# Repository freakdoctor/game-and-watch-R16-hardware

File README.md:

# game-and-watch-hardware

Basé sur le superbe travail d'Upcicle-Electronics pour les contours du PCB et le placement de certains composants.

Tentative de faire rentrer le hardware d'une SNES Mini dans une Game & Watch dans l'espoir d'y faire tourner le remaster Super Nes des premiers Marios inclus dans Super Mario All Stars.

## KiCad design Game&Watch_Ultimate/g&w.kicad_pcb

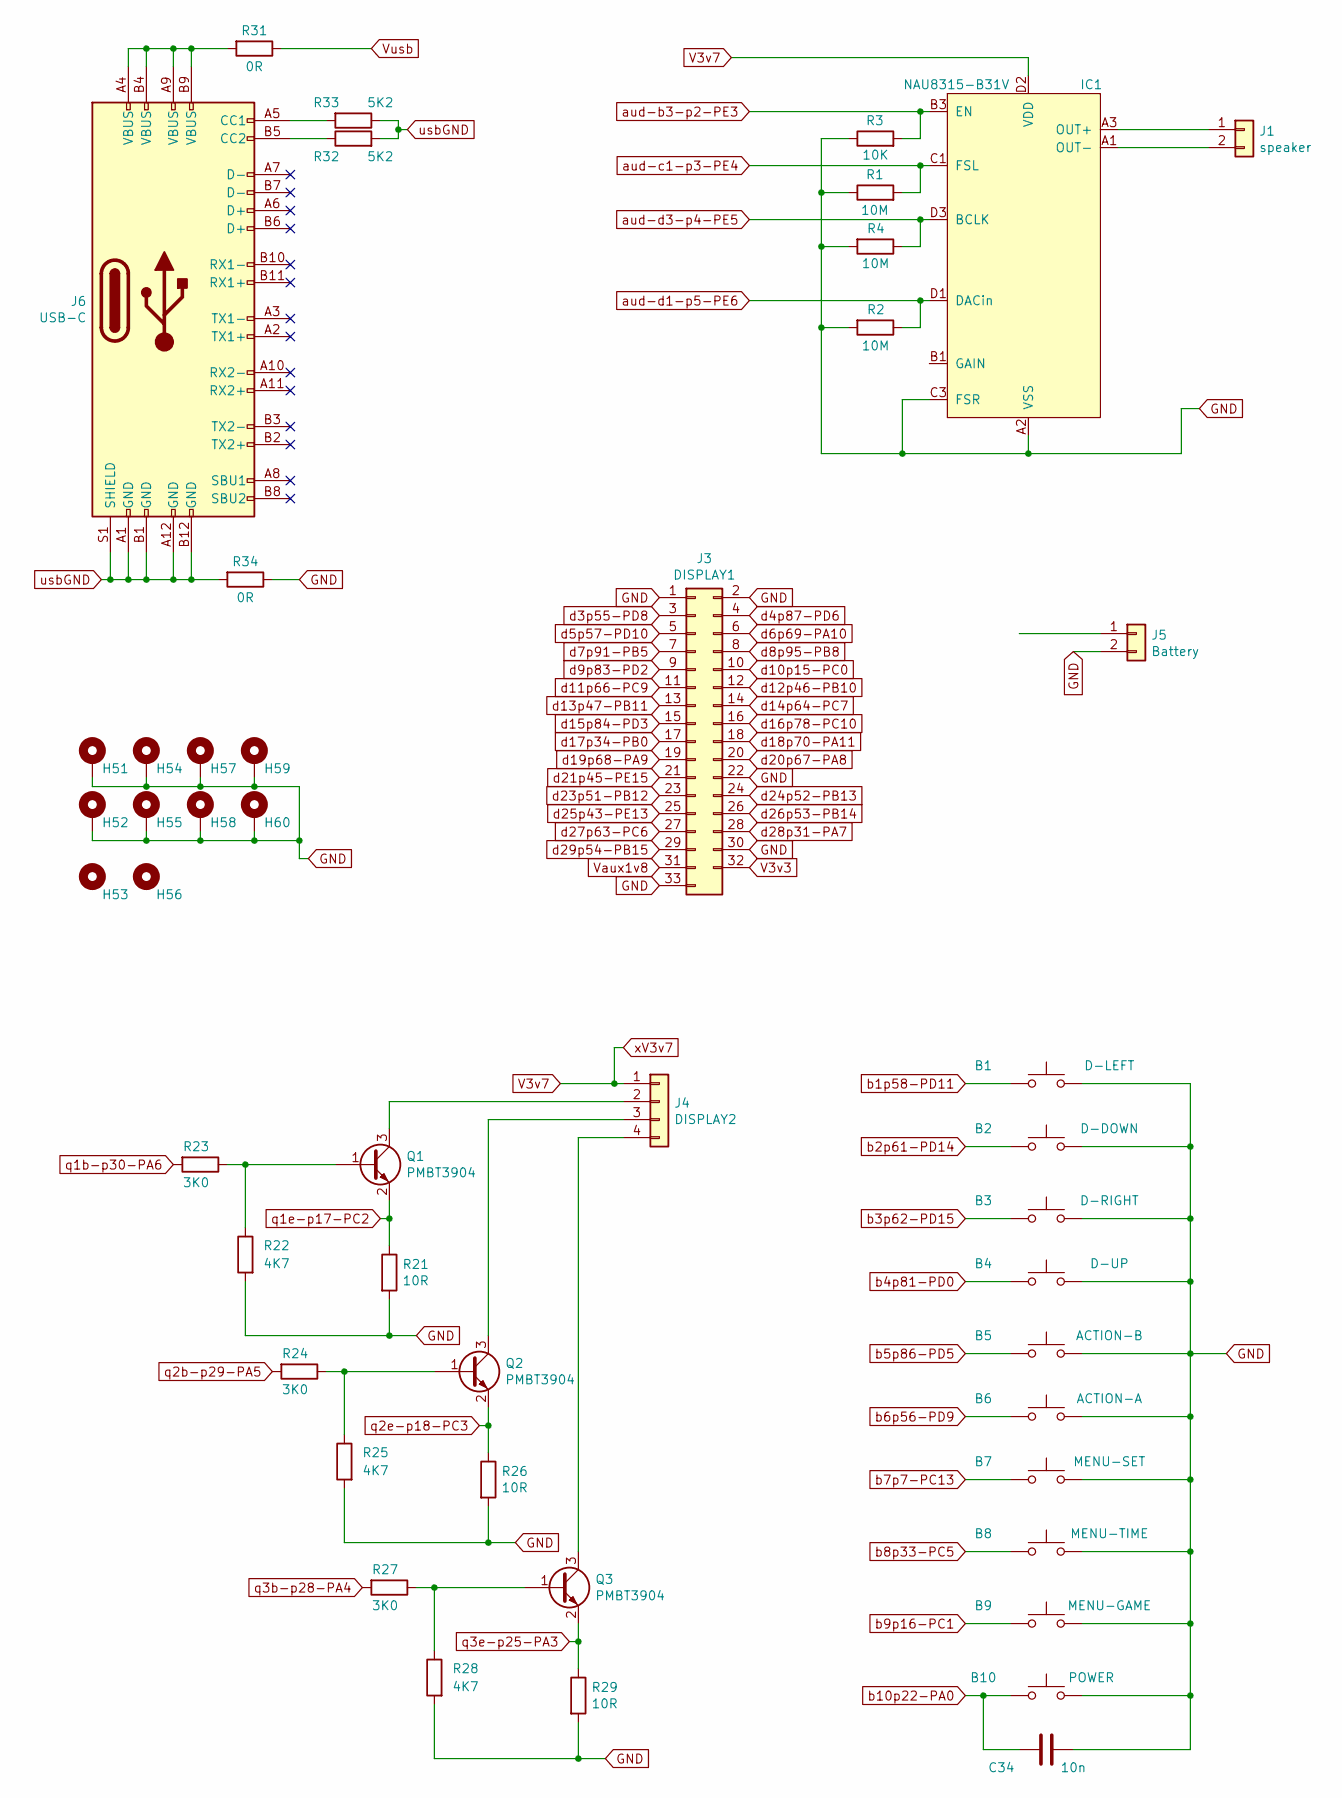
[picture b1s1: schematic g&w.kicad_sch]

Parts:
B1: D-LEFT; Button_Carbon-Contact_Round_5.00mm
B2: D-DOWN; Button_Carbon-Contact_Round_5.00mm
B3: D-RIGHT; Button_Carbon-Contact_Round_5.00mm
B4: D-UP; Button_Carbon-Contact_Round_5.00mm
B5: ACTION-B; Button_Carbon-Contact_Round_6.5mm
B6: ACTION-A; Button_Carbon-Contact_Round_6.5mm
B7: MENU-SET; Button_Carbon-Contact_Round_5.00mm
B8: MENU-TIME; Button_Carbon-Contact_Round_5.00mm
B9: MENU-GAME; Button_Carbon-Contact_Round_5.00mm
B10: POWER; SW_PUSH_1P1T_Horizontal_Nintendo_GnW
C34: 10n; C_0201_0603Metric
H51, H52, H54, H55, H57, H58, H59, H60: MountingHole_Pad; MountingHole_2.0mm
H53: MountingHole; MountingSlot_NC_1.3x2.2mm
H56: MountingHole; MountingHole_NC_1.5mm
IC1: NAU8315-B31V; WLCSP-12_1.18x1.95_Layout3x4_P0.4mm
J1: speaker; Speaker
J3: DISPLAY1; Molex_502078-3310_2Rows-33Pins-1MP_P0.5mm-int0.25mm_Horizon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
J4: DISPLAY2; Molex_Easy-On_503480-0400_1x04-1MP_P1.00mm_Horizontal
J5: Battery; Molex_Pico-EZmate_78171-0002_1x02-1MP_P1.20mm_Vertical
J6: USB-C; USB_C_Receptacle_JAE_DX07BN24JA2
Q1, Q2, Q3: PMBT3904; SOT-23
R1, R2, R4: 10M; R_0201_0603Metric
R3: 10K; R_0201_0603Metric
R21, R26, R29: 10R; R_0201_0603Metric
R22, R25, R28: 4K7; R_0201_0603Metric
R23, R24, R27: 3K0; R_0201_0603Metric
R31: 0R; R_0402_1005Metric
R32, R33: 5K2; R_0201_0603Metric
R34: 0R; R_0603_1608Metric

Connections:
GND: B1.2, B2.2, B3.2, B4.2, B5.2, B6.2, B7.2, B8.2, B9.2, B10.1, C34.2, H51.1, H52.1, H54.1, H55.1, H57.1, H58.1, H59.1, H60.1, IC1.A2 (VSS), IC1.C3 (FSR), J3.1, J3.2, J3.22, J3.30, J3.33, J5.2, R1.1, R2.2, R3.1, R4.2, R21.2, R22.2, R25.2, R26.2, R28.2, R29.2, R34.1
unnamed: IC1.D3 (BCLK), R4.1
unnamed: IC1.A3 (OUT+), J1.1
unnamed: IC1.A1 (OUT-), J1.2
unnamed: J4.2, Q1.3 (C)
unnamed: J4.3, Q2.3 (C)
unnamed: J4.4, Q3.3 (C)
unnamed: J6.A5 (CC1), R33.2
unnamed: J6.B5 (CC2), R32.1
unnamed: J6.A4 (VBUS), J6.A9 (VBUS), J6.B4 (VBUS), J6.B9 (VBUS), R31.2
unnamed: Q1.1 (B), R22.1, R23.1
unnamed: Q2.1 (B), R24.1, R25.1
unnamed: Q3.1 (B), R27.1, R28.1
V3v3: J3.32
V3v7: IC1.B2 (VDD), IC1.C2 (VDD), IC1.D2 (VDD), J4.1
Vaux1v8: J3.31
Vusb: R31.1
aud-b3-p2-PE3: IC1.B3 (EN), R3.2
aud-c1-p3-PE4: IC1.C1 (FSL), R1.2
aud-d1-p5-PE6: IC1.D1 (DACin), R2.1
b1p58-PD11: B1.1
b2p61-PD14: B2.1
b3p62-PD15: B3.1
b4p81-PD0: B4.1
b5p86-PD5: B5.1
b6p56-PD9: B6.1
b7p7-PC13: B7.1
b8p33-PC5: B8.1
b9p16-PC1: B9.1
b10p22-PA0: B10.2, C34.1
d3p55-PD8: J3.3
d4p87-PD6: J3.4
d5p57-PD10: J3.5
d6p69-PA10: J3.6
d7p91-PB5: J3.7
d8p95-PB8: J3.8
d9p83-PD2: J3.9
d10p15-PC0: J3.10
d11p66-PC9: J3.11
d12p46-PB10: J3.12
d13p47-PB11: J3.13
d14p64-PC7: J3.14
d15p84-PD3: J3.15
d16p78-PC10: J3.16
d17p34-PB0: J3.17
d18p70-PA11: J3.18
d19p68-PA9: J3.19
d20p67-PA8: J3.20
d21p45-PE15: J3.21
d23p51-PB12: J3.23
d24p52-PB13: J3.24
d25p43-PE13: J3.25
d26p53-PB14: J3.26
d27p63-PC6: J3.27
d28p31-PA7: J3.28
d29p54-PB15: J3.29
q1b-p30-PA6: R23.2
q1e-p17-PC2: Q1.2 (E), R21.1
q2b-p29-PA5: R24.2
q2e-p18-PC3: Q2.2 (E), R26.1
q3b-p28-PA4: R27.2
q3e-p25-PA3: Q3.2 (E), R29.1
usbGND: J6.A1 (GND), J6.A12 (GND), J6.B1 (GND), J6.B12 (GND), J6.S1 (SHIELD), R32.2, R33.1, R34.2

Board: 4 copper layers, 47 parts (9 on the bottom side), 22 nets, no tracks yet.

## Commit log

2023-04-17 My work Upload
2023-04-17 visuels
2023-04-17 No ROMs
2023-04-17 menage
2023-05-13 Hardware maj

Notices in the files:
Game&Watch_Ultimate/g&w.kicad_sch:
Licensed under the MIT License.
Copyright (c) 2021 Jake Little
